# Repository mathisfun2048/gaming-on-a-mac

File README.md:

# Gaming on a Mac

## What is this?
 - Mechanichal D-pad through arrow key and wasd layers
 - Also has buttons for shift, escape, tab, space
 - Button layout displayed on oled
 - Layers can be switched with the encoder or the bottom middle button

## How can I make it?
Read hardware_instructions.md! It walks through how many of what to buy, how to order the PCB, and how to assemble it together. 

## Demo
Here's a youtube link:

https://youtube.com/shorts/ai6QLhHT9NE?si=4pOMcnLnvPT2tYLt

## Pictures

PCB Schematic: 

In action:

## Where is the firmware I can flash?
It's in 2 places: you can either find the .uf2 file in the build directory, or, you can download the latest release on github!

If you make changes and need to recompile, follow the directions in firmware_instructions.md

## Cost?
As usual, free 99

## License
GNU GLP (if you use this, make sure your work is also open source!)

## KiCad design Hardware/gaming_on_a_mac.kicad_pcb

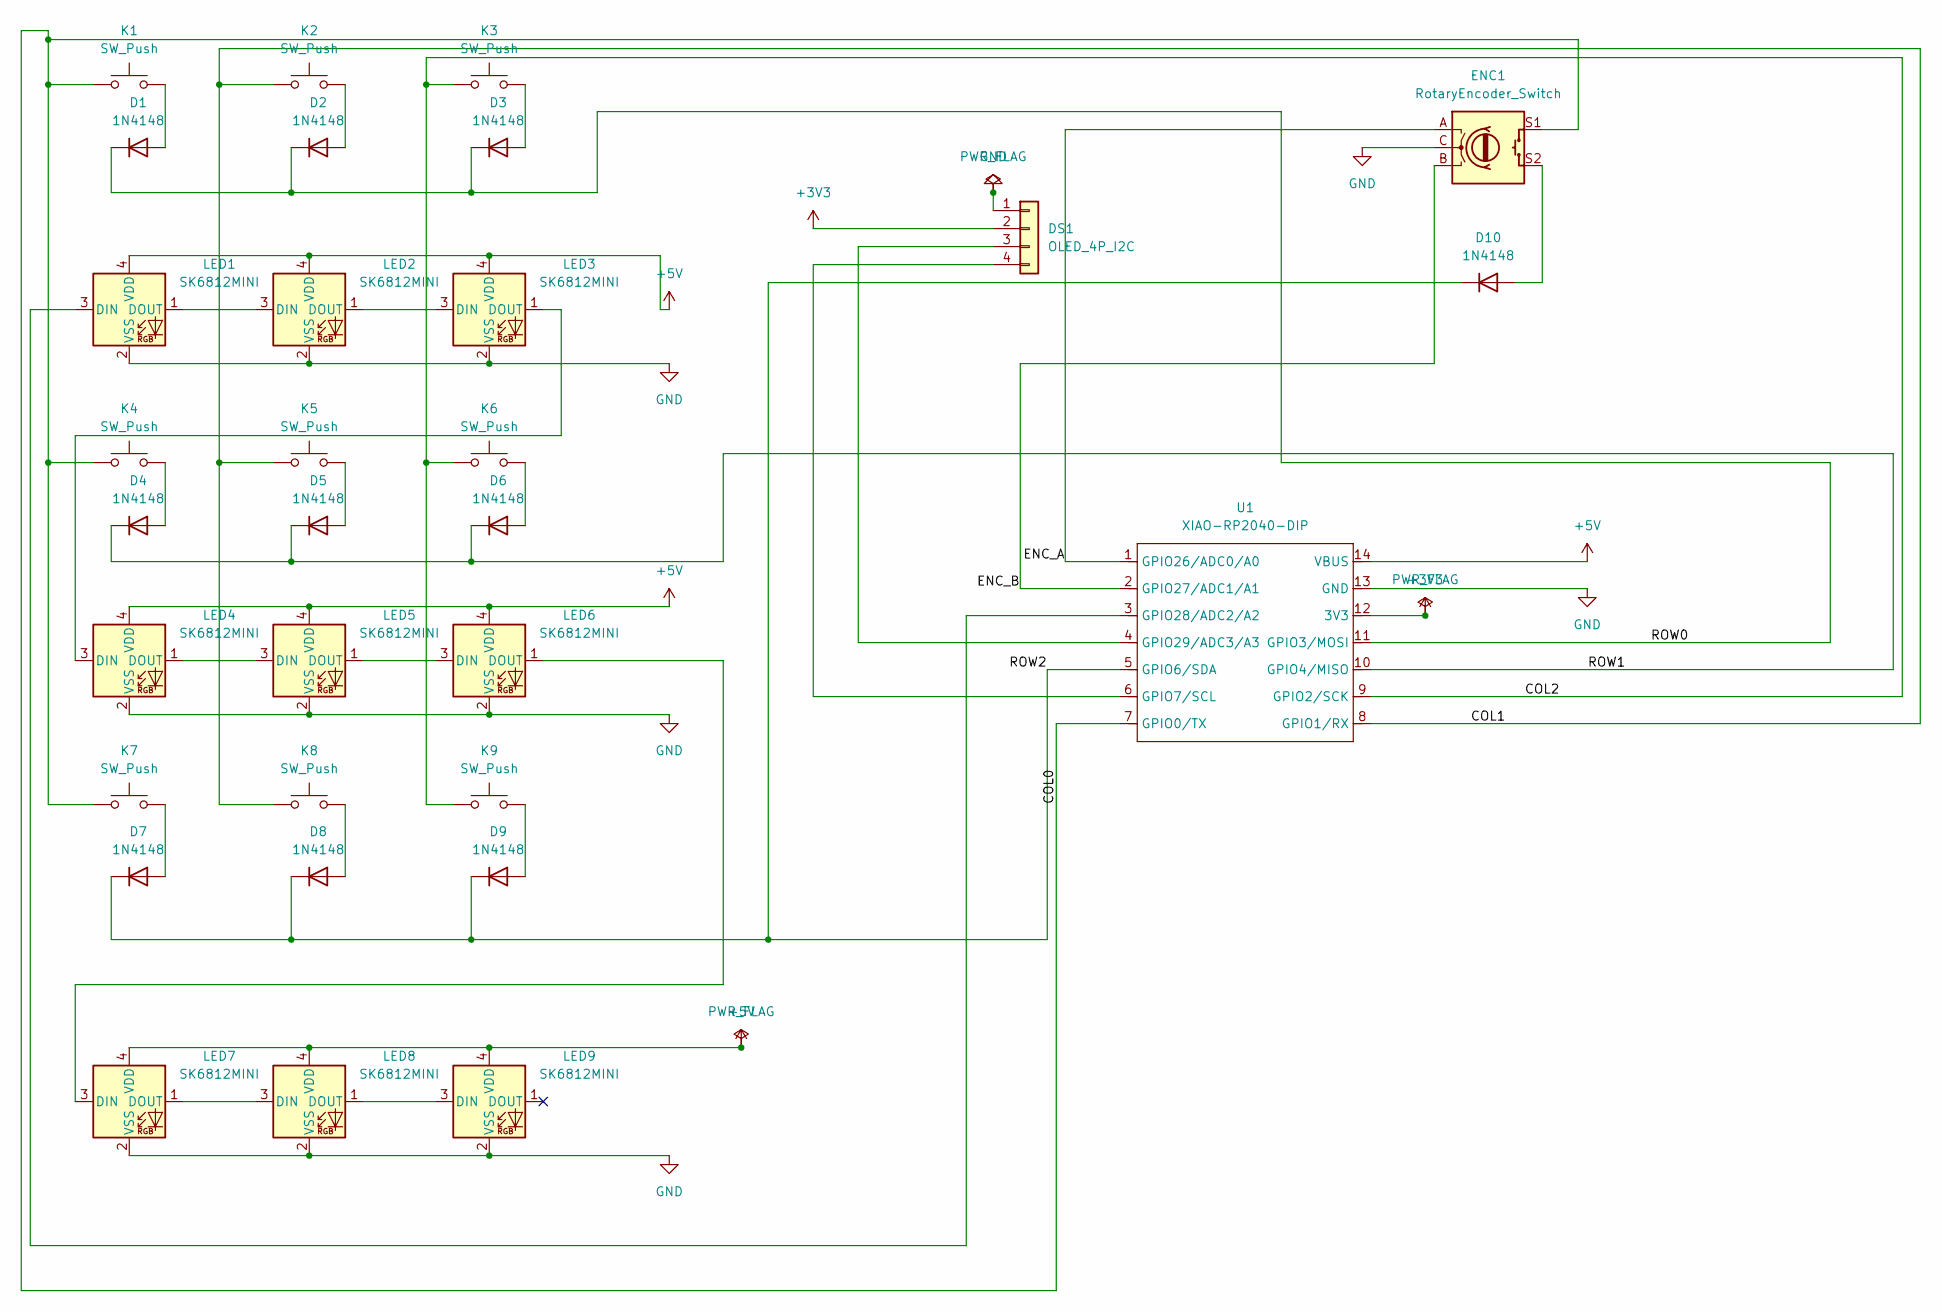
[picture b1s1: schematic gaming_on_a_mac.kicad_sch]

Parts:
D1, D2, D3, D4, D5, D6, D7, D8, D9, D10: 1N4148; D_DO-41_SOD81_P10.16mm_Horizontal
DS1: OLED_4P_I2C; SSD1306-0.91-OLED-4pin-128x32
ENC1: RotaryEncoder_Switch; RotaryEncoder_Alps_EC11E-Switch_Vertical_H20mm
K1, K2, K3, K4, K5, K6, K7, K8, K9: SW_Push; SW_Cherry_MX_1.00u_PCB
LED1, LED2, LED3, LED4, LED5, LED6, LED7, LED8, LED9: SK6812MINI; LED_SK6812MINI_PLCC4_3.5x3.5mm_P1.75mm
U1: XIAO-RP2040-DIP

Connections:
+3V3: DS1.2 (VCC), U1.12 (3V3)
+5V: LED1.4 (VDD), LED2.4 (VDD), LED3.4 (VDD), LED4.4 (VDD), LED5.4 (VDD), LED6.4 (VDD), LED7.4 (VDD), LED8.4 (VDD), LED9.4 (VDD), U1.14 (VBUS)
/COL0: ENC1.S1, K1.1, K4.1, K7.1, U1.7 (GPIO0/TX)
/COL1: K2.1, K5.1, K8.1, U1.8 (GPIO1/RX)
/COL2: K3.1, K6.1, K9.1, U1.9 (GPIO2/SCK)
/ENC_A: ENC1.A, U1.1 (GPIO26/ADC0/A0)
/ENC_B: ENC1.B, U1.2 (GPIO27/ADC1/A1)
/ROW0: D1.1 (K), D2.1 (K), D3.1 (K), U1.11 (GPIO3/MOSI)
/ROW1: D4.1 (K), D5.1 (K), D6.1 (K), U1.10 (GPIO4/MISO)
/ROW2: D7.1 (K), D8.1 (K), D9.1 (K), D10.1 (K), U1.5 (GPIO6/SDA)
GND: DS1.1 (GND), ENC1.C, LED1.2 (VSS), LED2.2 (VSS), LED3.2 (VSS), LED4.2 (VSS), LED5.2 (VSS), LED6.2 (VSS), LED7.2 (VSS), LED8.2 (VSS), LED9.2 (VSS), U1.13 (GND)
unnamed: D1.2 (A), K1.2
unnamed: D2.2 (A), K2.2
unnamed: D3.2 (A), K3.2
unnamed: D4.2 (A), K4.2
unnamed: D5.2 (A), K5.2
unnamed: D6.2 (A), K6.2
unnamed: D7.2 (A), K7.2
unnamed: D8.2 (A), K8.2
unnamed: D9.2 (A), K9.2
unnamed: D10.2 (A), ENC1.S2
unnamed: DS1.3 (SCL), U1.4 (GPIO29/ADC3/A3)
unnamed: DS1.4 (SDA), U1.6 (GPIO7/SCL)
unnamed: LED1.3 (DIN), U1.3 (GPIO28/ADC2/A2)
unnamed: LED1.1 (DOUT), LED2.3 (DIN)
unnamed: LED2.1 (DOUT), LED3.3 (DIN)
unnamed: LED3.1 (DOUT), LED4.3 (DIN)
unnamed: LED4.1 (DOUT), LED5.3 (DIN)
unnamed: LED5.1 (DOUT), LED6.3 (DIN)
unnamed: LED6.1 (DOUT), LED7.3 (DIN)
unnamed: LED7.1 (DOUT), LED8.3 (DIN)
unnamed: LED8.1 (DOUT), LED9.3 (DIN)

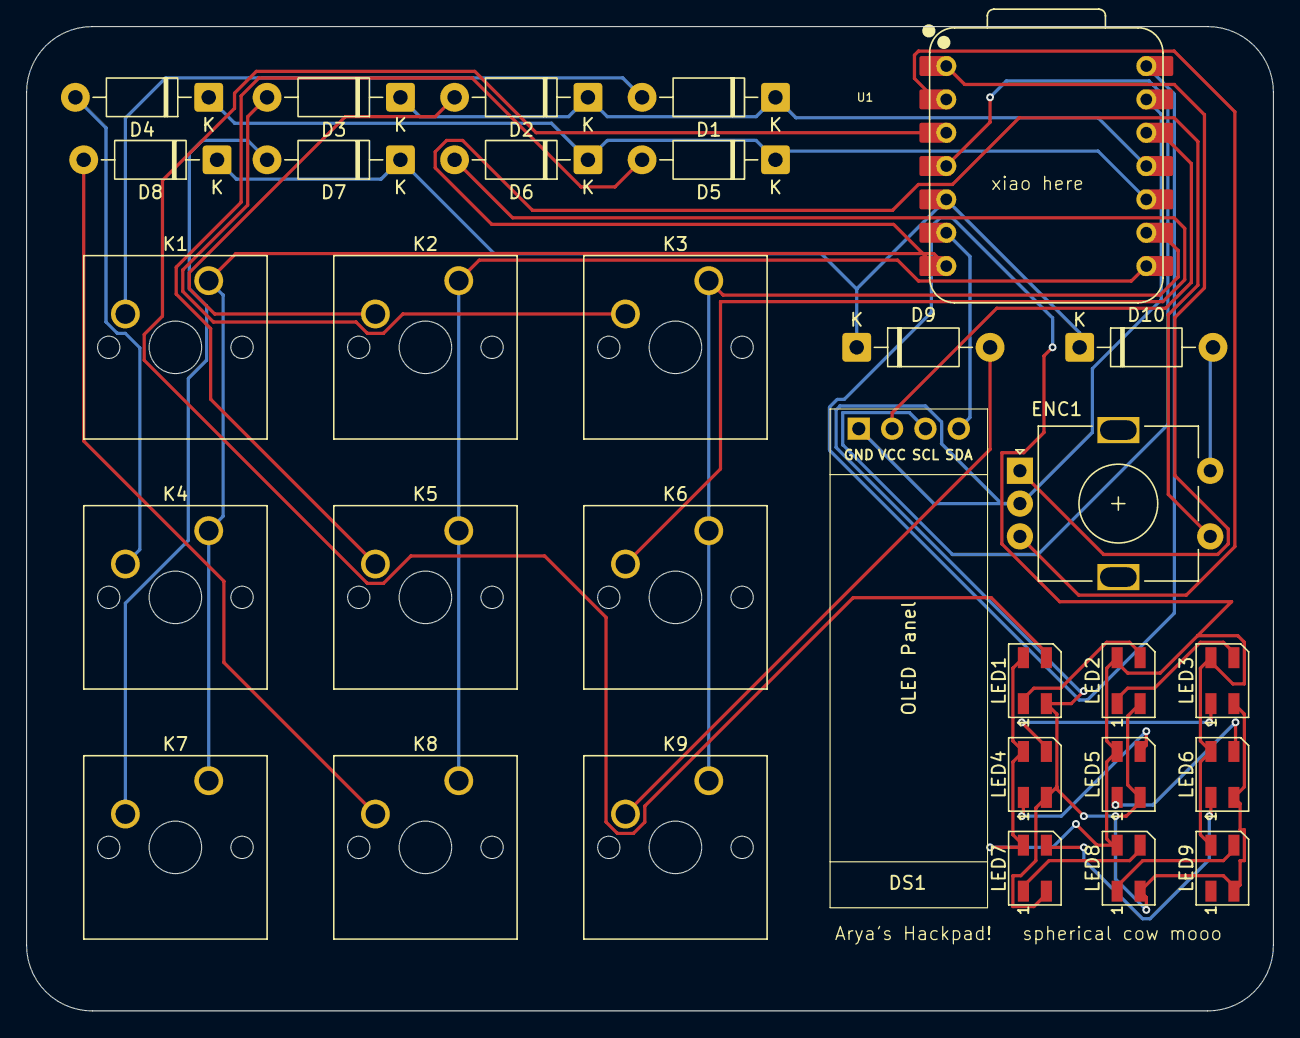
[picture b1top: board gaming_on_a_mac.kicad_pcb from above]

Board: 2 copper layers, 95.0 x 75.0 mm, 31 parts (0 on the bottom side), 32 nets.

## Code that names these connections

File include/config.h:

// the purpous of thsi document is to define hardware pin mapping
// this document is when it starts getting fun because its C and not CMake :)

#ifndef CONFIG_H // checks if macro does not exist
#define CONFIG_H // starts defining the macro

#define NUM_ROWS 3
#define NUM_COLS 3
/*
for my switch matrix I chose to implement a row-col system


row 1 -> 1 2 3
row 2 -> 4 5 6
row 3 -> 7 8 9

<cols not pictured becasue typing that is hard>
*/
#define DEBOUNCE_MS 5
// just defines how much time we expect the debouce of keys to be

#define COL1_PIN 0
#define COL2_PIN 1
#define COL3_PIN 2
// this indicates which gpios my col lines are connected to
// make sure you do teh GPIO pins, not the pin number

#define ROW1_PIN 3
#define ROW2_PIN 4
#define ROW3_PIN 6
// same thing as above
// theres a jump between 4 and 6 bc my mcu does not have a gpio 5 haha

#define ENCODER_A_PIN 26
#define ENCODER_B_PIN 27
// same thing but now for encoder pins

#define OLED_SCL_PIN 29
#define OLED_SDA_PIN 7
// same thing as before
// I cannot use defult SDA and SCL because I wired my pcb incorectly 
// so we will implement software I2C in this project

#define KEY_TOGGLE 7
// I plan to have multiple layers of up/down/left/right depending on game, and we need a toggle between those layers
// this makes index 7, key 8 (row 3 middle) to be the key that toggles!

#endif
// this closes the if statement we had in the begining

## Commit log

2025-12-25 finished CMakeLists.txt!
2025-12-26 created some files, and wrote config.h
2025-12-27 working on matrix functions
2025-12-27 finished matrix, i think
2025-12-27 finished the encoder
2025-12-28 working on oled implementation
2025-12-28 finished teh letters
2025-12-29 continuing to learn I2C
2025-12-29 continuing updates
2025-12-30 finished oled files
2025-12-30 finished tiny usb config
2025-12-30 working on usb_hid
2025-12-30 added hid calls
2025-12-31 finished usb descriptors
2025-12-31 working on overall implementation now!
2025-12-31 debugging
2025-12-31 version 1
2025-12-31 fixed bugs
2026-01-02 current implementation!
2026-01-02 wrote instructions for how to do hardware
2026-01-02 added hardware files
2026-01-02 added to hardware instructions and readme!
2026-01-02 renamed smth
